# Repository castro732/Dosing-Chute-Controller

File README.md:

#Dosing Chute Controller

## Description

Controller for a Dosing Chute using a Load Cell to measure weight. Implemented using an ATMEGA328P programmed with Arduino.

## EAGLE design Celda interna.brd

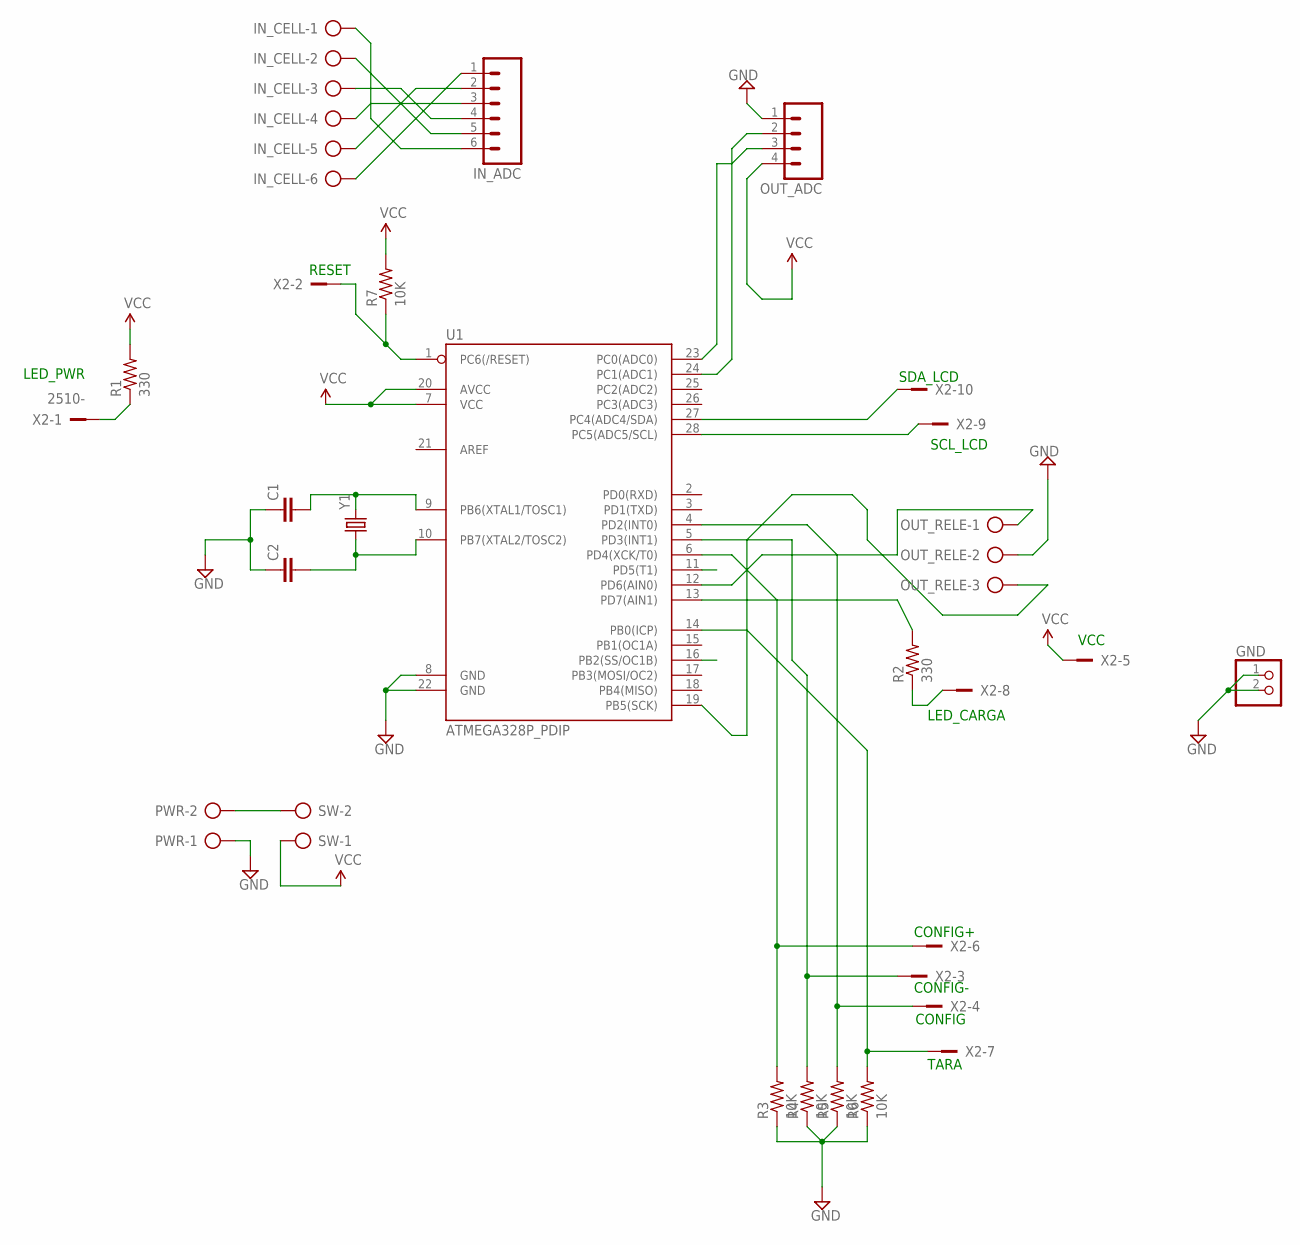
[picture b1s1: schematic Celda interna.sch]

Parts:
C1, C2: CAPKIT; CAP-PTH-SMALL-KIT
GND: PINHD-1X2; 1X02
IN_ADC: M06LONGPADS; 1X06_LONGPADS
IN_CELL: AK500/6
OUT_ADC: M04LONGPADS; 1X04_LONGPADS
OUT_RELE: AK500/3
PWR: AK500/2
R1, R2: 330; AXIAL-0.4
R3, R4, R5, R6, R7: 10K; AXIAL-0.4
SW: AK500/2
U1: ATMEGA328P_PDIP; DIL28-3
X2: 2510-; PAK100/2500-10
Y1: CRYSTALHC49US; HC49US

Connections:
GND: C1.1, C2.1, GND.1, GND.2, OUT_ADC.1, OUT_RELE.2, PWR.1, R3.P$1 (1), R4.P$1 (1), R5.P$1 (1), R6.P$1 (1), U1.8 (GND), U1.22 (GND)
unnamed: U1.28 (PC5(ADC5/SCL)), X2.9
unnamed: U1.27 (PC4(ADC4/SDA)), X2.10
unnamed: IN_ADC.1, IN_CELL.6
unnamed: IN_ADC.2, IN_CELL.5
unnamed: OUT_ADC.2, U1.24 (PC1(ADC1))
unnamed: OUT_ADC.3, U1.23 (PC0(ADC0))
unnamed: IN_ADC.3, IN_CELL.4
unnamed: IN_ADC.4, IN_CELL.3
unnamed: IN_ADC.5, IN_CELL.2
unnamed: IN_ADC.6, IN_CELL.1
unnamed: R3.P$2 (2), U1.6 (PD4(XCK/T0)), X2.6
unnamed: R1.P$1 (1), X2.1
unnamed: OUT_RELE.1, U1.12 (PD6(AIN0))
unnamed: C1.2, U1.9 (PB6(XTAL1/TOSC1)), Y1.2
unnamed: R2.P$1 (1), X2.8
unnamed: R2.P$2 (2), U1.13 (PD7(AIN1))
unnamed: R4.P$2 (2), U1.5 (PD3(INT1)), X2.3
unnamed: R5.P$2 (2), U1.4 (PD2(INT0)), X2.4
unnamed: R6.P$2 (2), U1.14 (PB0(ICP)), X2.7
unnamed: R7.P$1 (1), U1.1 (PC6(/RESET)), X2.2
unnamed: PWR.2, SW.2
unnamed: OUT_RELE.3, U1.19 (PB5(SCK))
unnamed: C2.2, U1.10 (PB7(XTAL2/TOSC2)), Y1.1
VCC: OUT_ADC.4, R1.P$2 (2), R7.P$2 (2), SW.1, U1.7 (VCC), U1.20 (AVCC), X2.5

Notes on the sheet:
TARA
CONFIG
CONFIG+
CONFIG-
VCC
LED_CARGA
SCL_LCD
SDA_LCD
LED_PWR
RESET

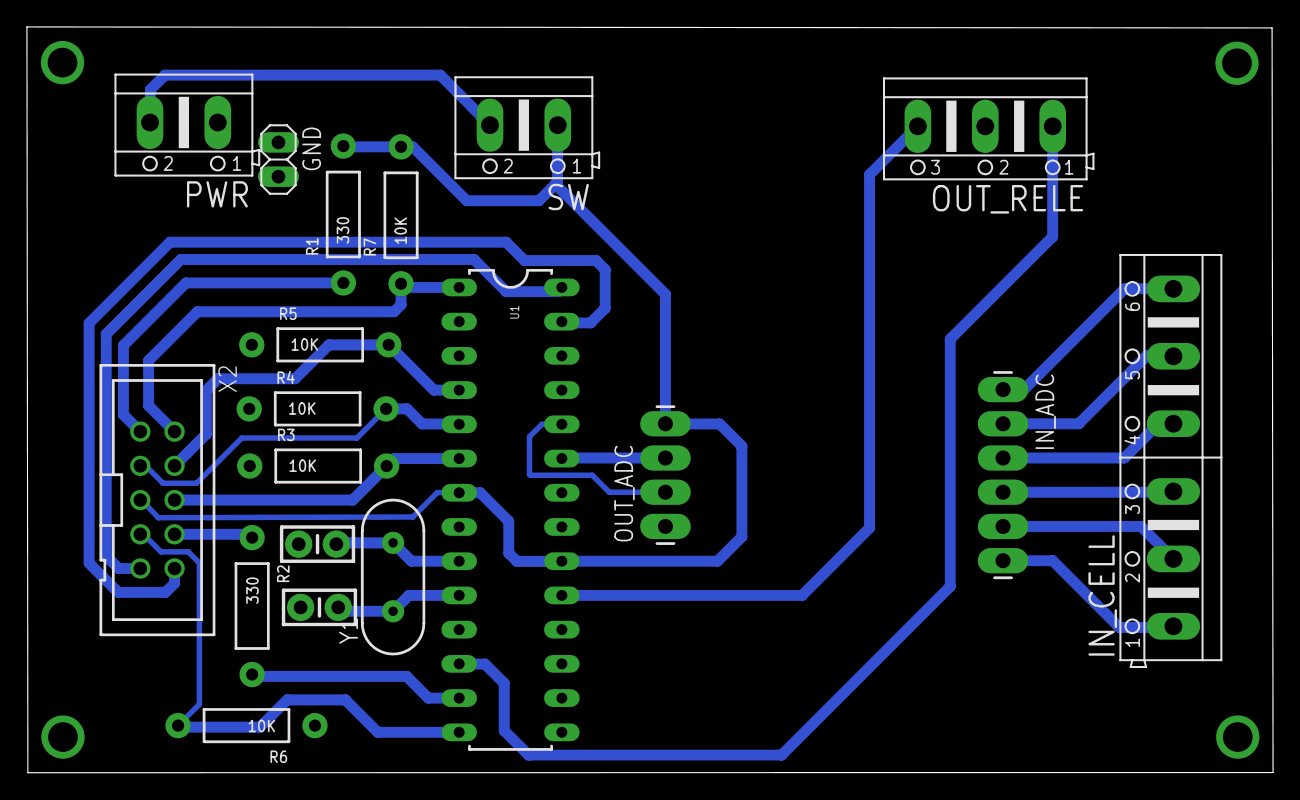
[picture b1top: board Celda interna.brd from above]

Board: 2 copper layers, 92.5 x 55.4 mm, 19 parts (0 on the bottom side), 25 nets.

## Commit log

2016-08-05 Add files
2016-08-06 Update logo

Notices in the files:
parts and their libraries:
SparkFun-Connectors: Licensing: Creative Commons ShareAlike 4.0 International - https://creativecommons.org/licenses/by-sa/4.0
